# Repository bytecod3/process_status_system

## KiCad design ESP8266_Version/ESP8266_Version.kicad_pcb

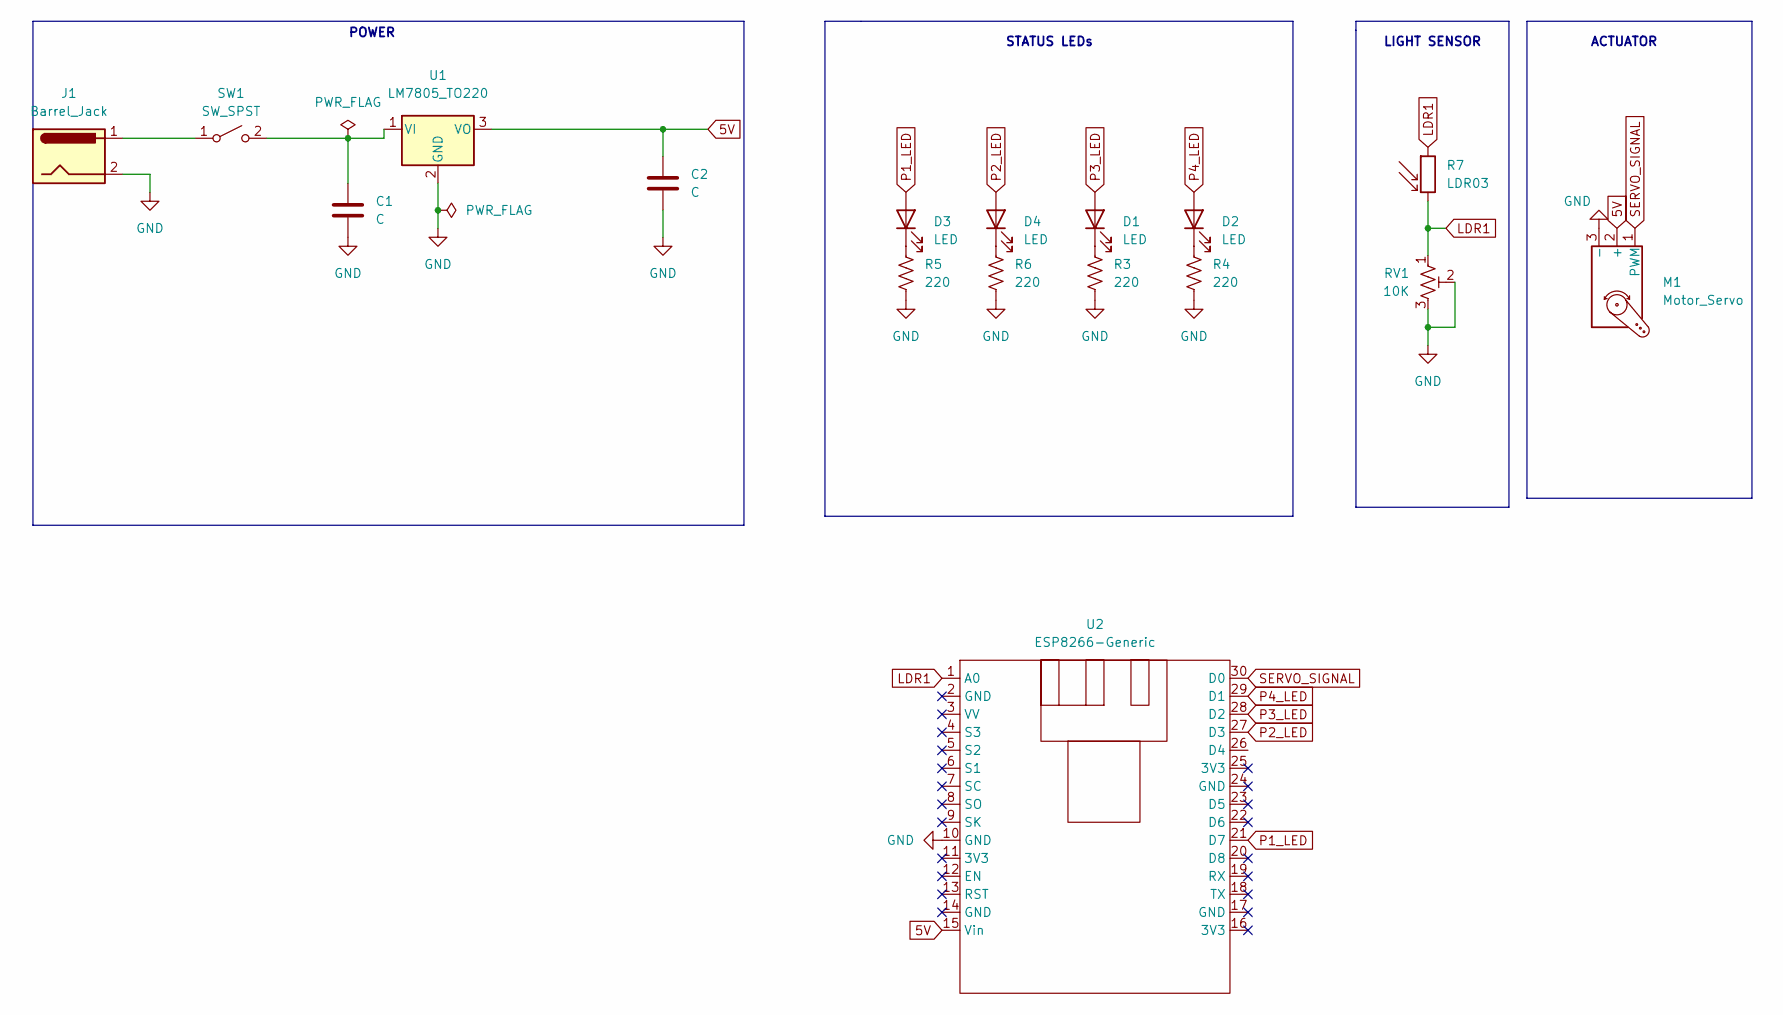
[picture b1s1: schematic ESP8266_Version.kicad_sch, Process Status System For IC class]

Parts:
C1, C2: C; CP_Radial_D4.0mm_P1.50mm
D1, D2, D3, D4: LED; LED_D5.0mm
J1: Barrel_Jack; BarrelJack_GCT_DCJ200-10-A_Horizontal
M1: Motor_Servo; PinHeader_1x03_P2.54mm_Vertical
R3, R4, R5, R6: 220; R_Axial_DIN0204_L3.6mm_D1.6mm_P7.62mm_Horizontal
R7: LDR03; R_LDR_10x8.5mm_P7.6mm_Vertical
RV1: 10K; Potentiometer_Piher_PT-10-V05_Vertical
SW1: SW_SPST; piano-slide-switchx3
U1: LM7805_TO220; TO-220-3_Vertical
U2: ESP8266-Generic

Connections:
5V: C2.1, M1.2 (+), U1.3 (VO), U2.15 (Vin)
GND: C1.2, C2.2, J1.2, M1.3 (-), R3.2, R4.2, R5.2, R6.2, RV1.2, RV1.3, U1.2 (GND), U2.10 (GND)
LDR1: R7.1, R7.2, RV1.1, U2.1 (A0)
unnamed: C1.1, SW1.2 (B), U1.1 (VI)
unnamed: D1.1 (K), R3.1
unnamed: D2.1 (K), R4.1
unnamed: D3.1 (K), R5.1
unnamed: D4.1 (K), R6.1
unnamed: J1.1, SW1.1 (A)
P1_LED: D3.2 (A), U2.21 (D7)
P2_LED: D4.2 (A), U2.27 (D3)
P3_LED: D1.2 (A), U2.28 (D2)
P4_LED: D2.2 (A), U2.29 (D1)
SERVO_SIGNAL: M1.1 (PWM), U2.30 (D0)

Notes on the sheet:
LIGHT SENSOR
ACTUATOR
POWER
STATUS LEDs

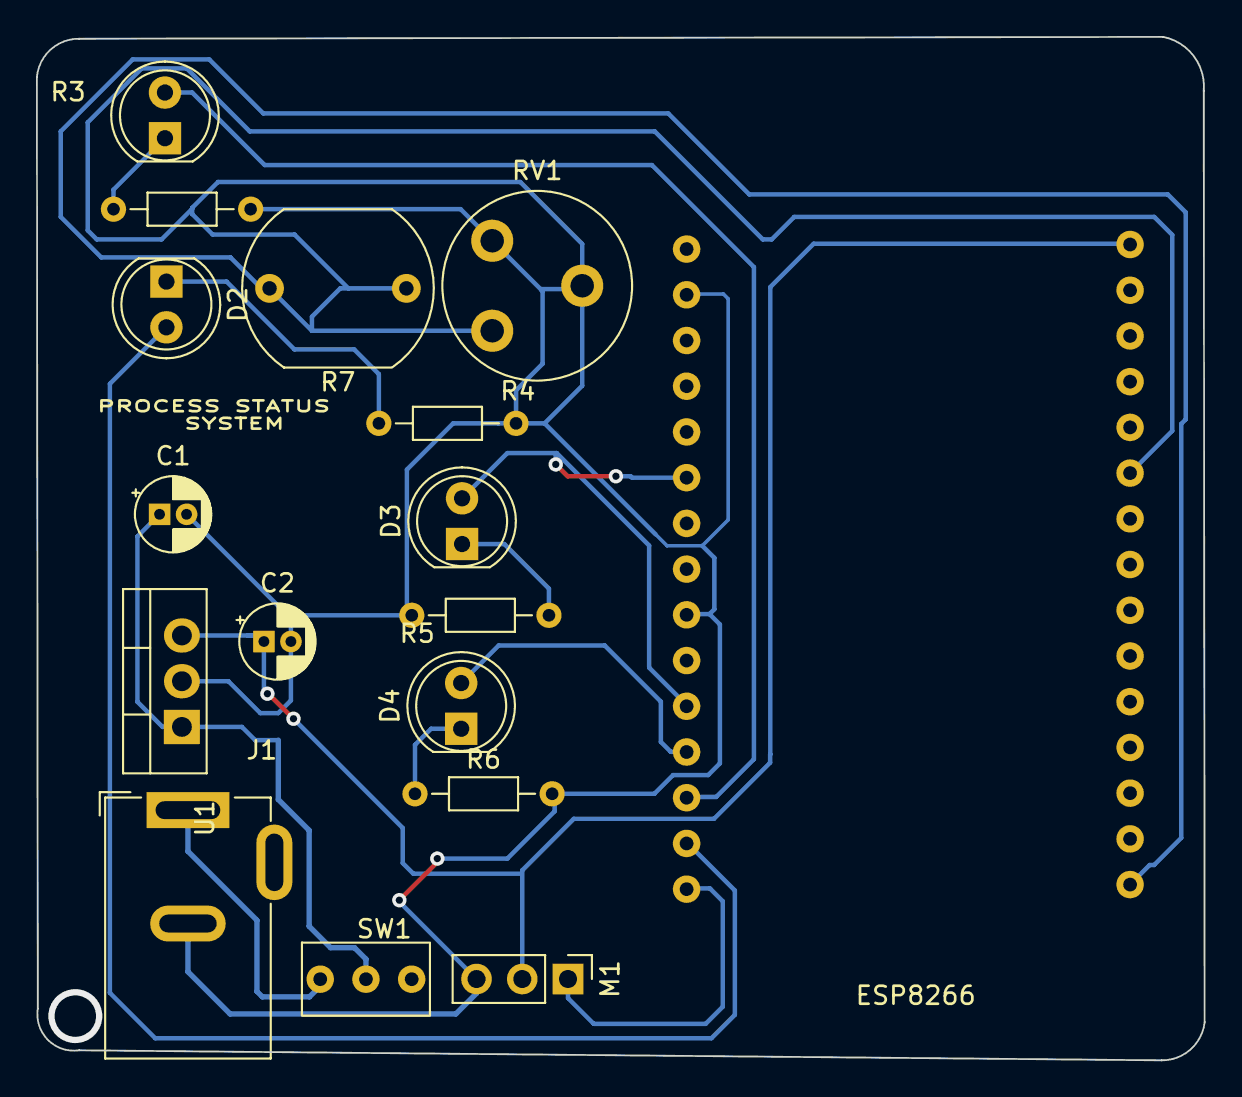
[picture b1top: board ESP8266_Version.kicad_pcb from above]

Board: 2 copper layers, 64.9 x 56.9 mm, 17 parts (0 on the bottom side), 14 nets.

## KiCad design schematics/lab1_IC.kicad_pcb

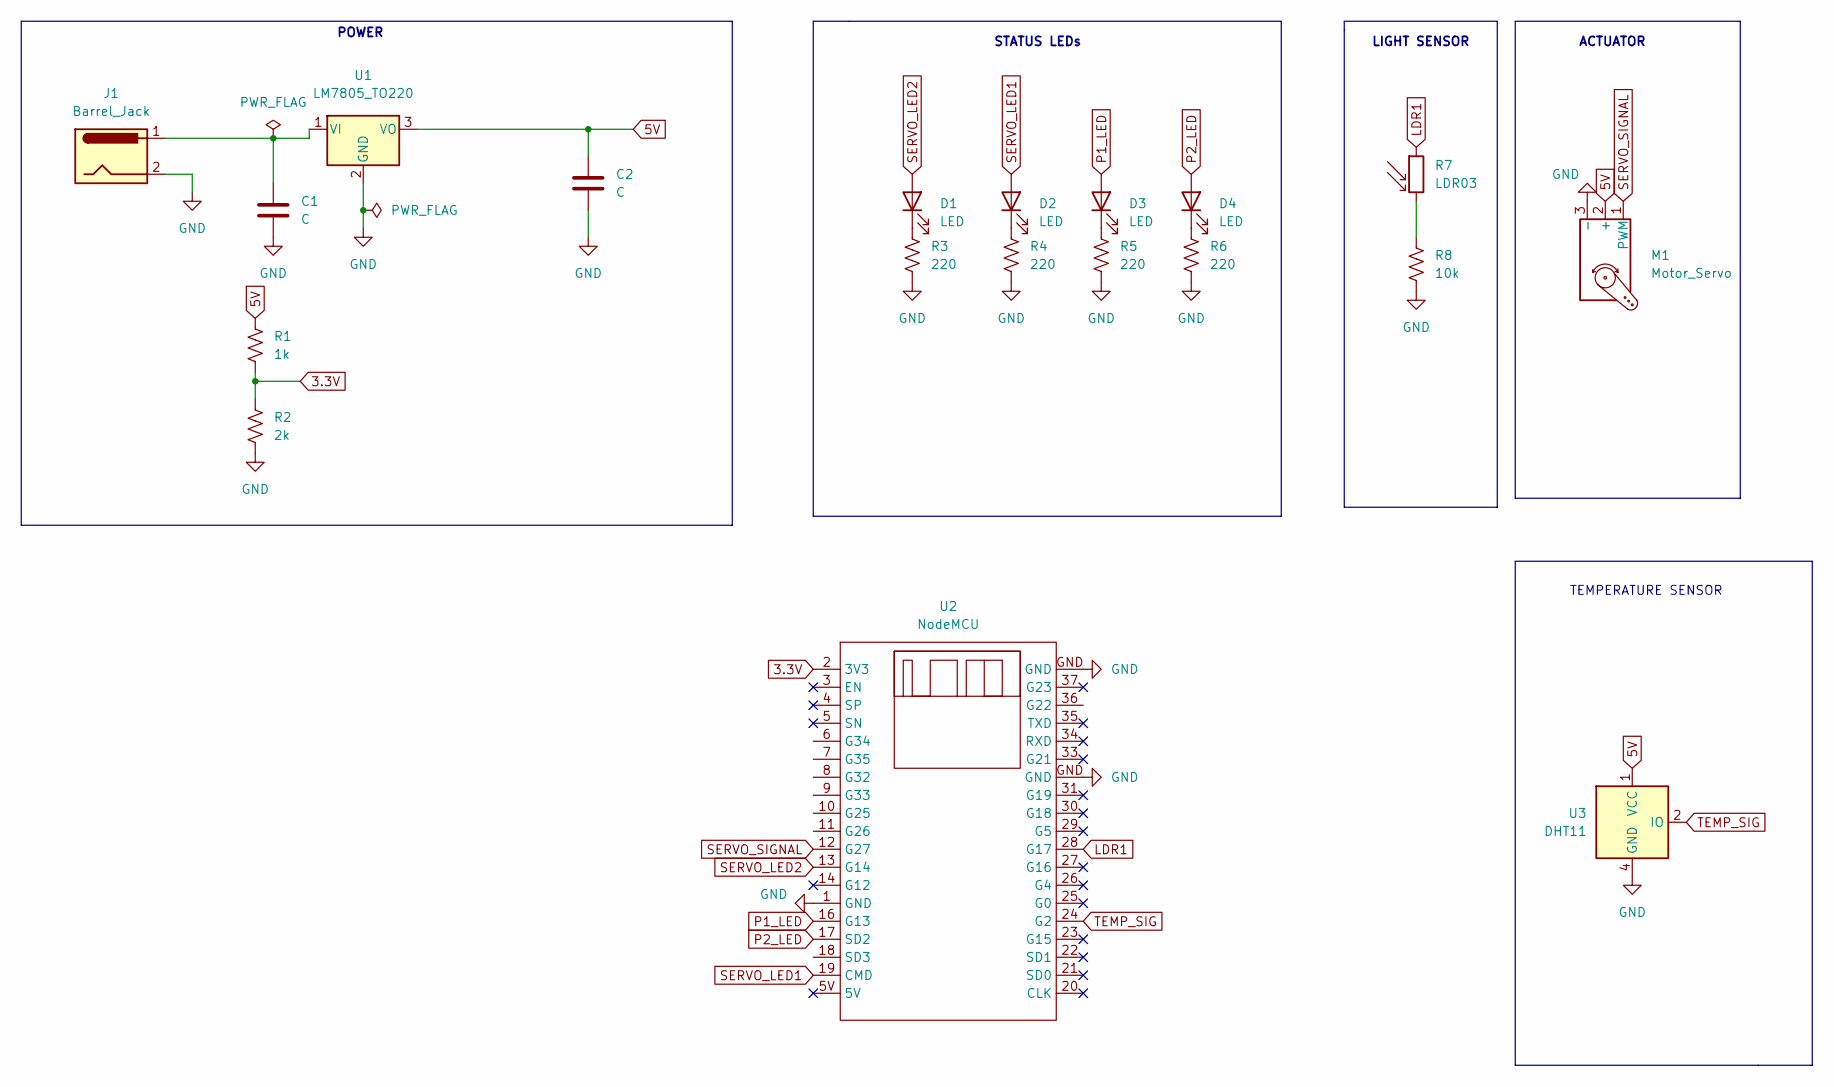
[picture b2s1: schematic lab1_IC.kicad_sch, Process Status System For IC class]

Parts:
C1, C2: C; CP_Radial_D8.0mm_P2.50mm
D1, D2, D3, D4: LED; LED_D5.0mm
J1: Barrel_Jack; BarrelJack_GCT_DCJ200-10-A_Horizontal
M1: Motor_Servo; PinHeader_1x03_P2.54mm_Vertical
R1: 1k; R_Axial_DIN0204_L3.6mm_D1.6mm_P7.62mm_Horizontal
R2: 2k; R_Axial_DIN0204_L3.6mm_D1.6mm_P7.62mm_Horizontal
R3, R4, R5, R6: 220; R_Axial_DIN0204_L3.6mm_D1.6mm_P7.62mm_Horizontal
R7: LDR03; R_LDR_10x8.5mm_P7.6mm_Vertical
R8: 10k; R_Axial_DIN0204_L3.6mm_D1.6mm_P7.62mm_Horizontal
U1: LM7805_TO220; TO-220-3_Vertical
U2: NodeMCU; ESP32-DOIT-DEVKIT
U3: DHT11; Aosong_DHT11_5.5x12.0_P2.54mm

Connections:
3.3V: R1.2, R2.1, U2.2 (3V3)
5V: C2.1, M1.2 (+), R1.1, U1.3 (VO), U3.1 (VCC)
GND: C1.2, C2.2, J1.2, M1.3 (-), R2.2, R3.2, R4.2, R5.2, R6.2, R8.2, U1.2 (GND), U2.1 (GND), U2.GND, U3.4 (GND)
LDR1: R7.1, U2.28 (G17)
unnamed: C1.1, J1.1, U1.1 (VI)
unnamed: D1.1 (K), R3.1
unnamed: D2.1 (K), R4.1
unnamed: D3.1 (K), R5.1
unnamed: D4.1 (K), R6.1
unnamed: R7.2, R8.1
P1_LED: D3.2 (A), U2.16 (G13)
P2_LED: D4.2 (A), U2.17 (SD2)
SERVO_LED1: D2.2 (A), U2.19 (CMD)
SERVO_LED2: D1.2 (A), U2.13 (G14)
SERVO_SIGNAL: M1.1 (PWM), U2.12 (G27)
TEMP_SIG: U2.24 (G2), U3.2 (IO)

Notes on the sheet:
LIGHT SENSOR
ACTUATOR
POWER
STATUS LEDs
TEMPERATURE SENSOR

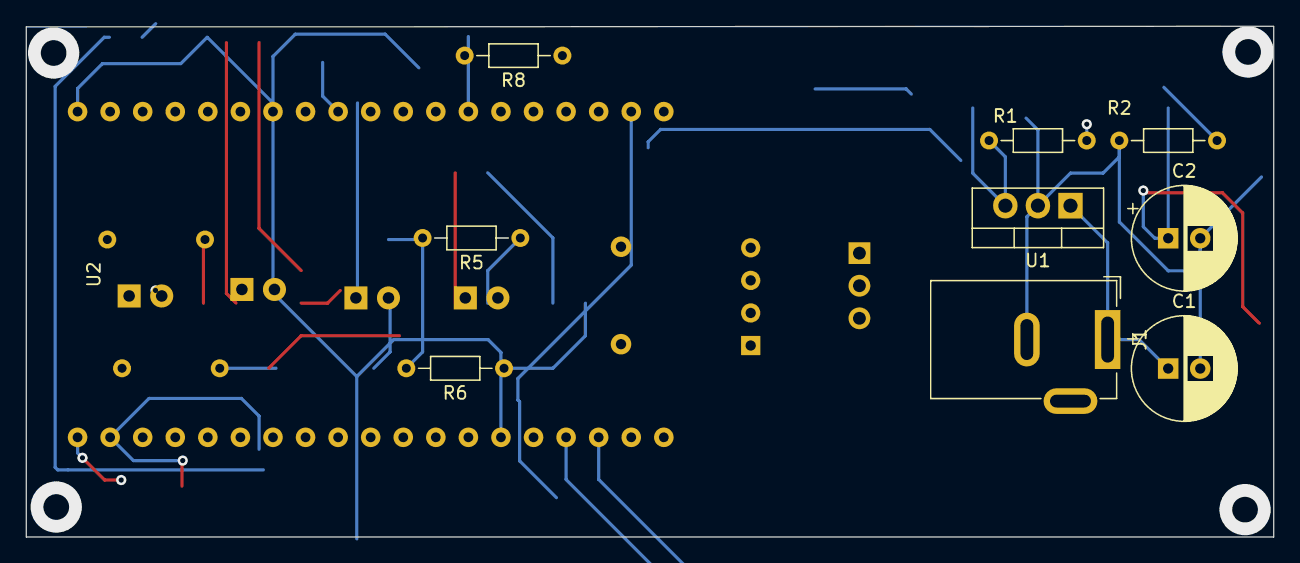
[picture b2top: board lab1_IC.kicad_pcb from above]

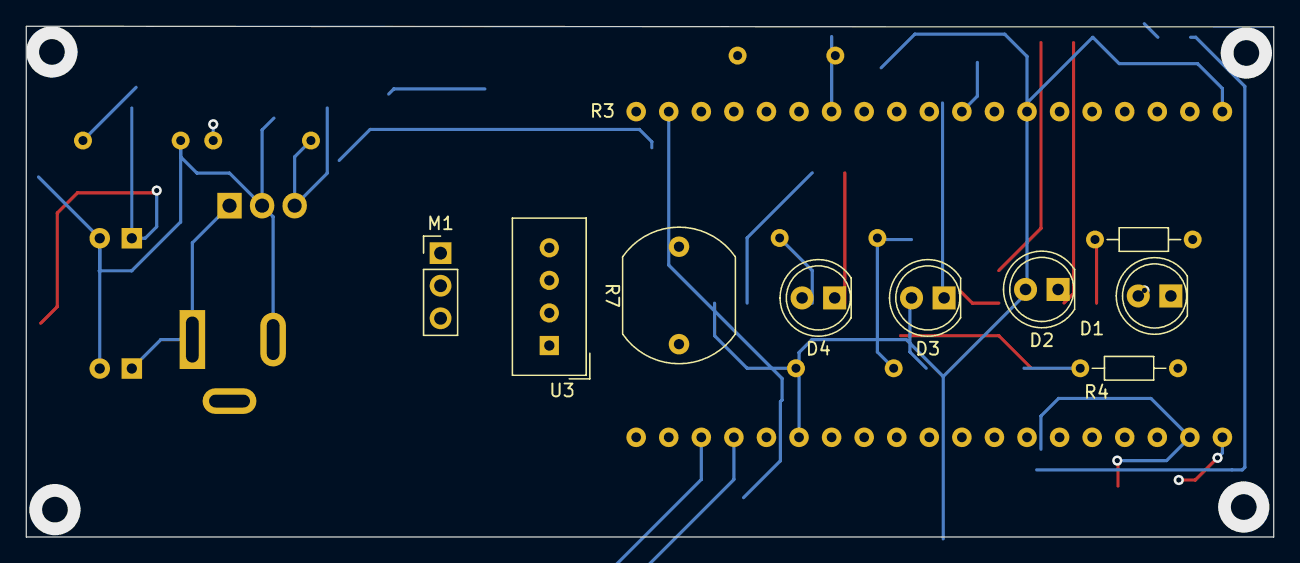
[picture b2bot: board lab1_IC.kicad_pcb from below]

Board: 2 copper layers, 97.3 x 39.8 mm, 19 parts (9 on the bottom side), 16 nets.

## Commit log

2022-06-17 initial
2022-06-17 added schematics
2022-06-17 added SPIFFS test files
2022-06-24 added server config
2022-07-01 fritzing
2022-07-01 test file
2022-07-01 added Readme folder
2022-07-01 readme folder
2022-07-01 added: servo functions to firmware
2022-07-01 added: gitignore
2022-07-18 added: esp8266 version:
